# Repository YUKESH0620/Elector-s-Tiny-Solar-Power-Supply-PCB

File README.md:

# Elektor’s Solar Power Supply – Learning-Oriented Redesign

## 1. Project Overview
This project is a learning-focused redesign of **Elektor’s Tiny Solar Power Supply**. The aim is to understand the fundamentals of solar energy harvesting and low-power power supply design through hands-on schematic capture and PCB layout.

The entire circuit and PCB were redesigned from scratch using **KiCad EDA**, while referring to the original Elektor concept **strictly for educational and learning purposes**. This project emphasizes clarity, simplicity, and real-world design thinking rather than product optimization.

---

## 2. Key Learning Objectives
- Understanding **solar input conditioning** and handling variable input sources  
- Learning **power regulation basics** for low-power applications  
- Developing **component selection reasoning** based on electrical and practical constraints  
- Applying **practical PCB layout considerations** such as trace routing, grounding, and component placement  

---

## 3. Tools & Software Used
- **KiCad EDA**
  - Schematic Editor  
  - PCB Layout Editor  
  - 3D Viewer  

---

## 4. Project Files
- Schematic design files (`.kicad_sch`)  
- PCB layout files (`.kicad_pcb`)  
- 3D render images  
- Manufacturing-ready Gerber files  

---

## 5. Block-Level Working Explanation
The system starts with a **solar panel** as the primary energy source. Since solar output varies with light conditions, the input stage conditions and stabilizes this energy before it is used further.

The conditioned solar input is then passed to a **DC-DC regulation stage**, which converts the variable input voltage into a usable and stable output suitable for low-power electronic circuits. Passive components around the regulator help improve stability and efficiency.

Finally, the regulated output is made available through the output terminals, allowing it to power small loads or act as a learning reference for energy-harvesting power supplies.

This block-level flow helps beginners understand how energy moves through the system without diving into complex mathematical analysis.

---

## 6. Bill of Materials (BOM)

| S.No | Reference | Component Type        | Value / Part Number        | Footprint     | Quantity | Description |
|------|-----------|----------------------|----------------------------|---------------|----------|-------------|
| 1    | U1        | DC-DC Boost Converter| AP3015AKTR-G1               | SOT-23-5     | 1        | Step-up DC-DC converter |
| 2    | L1        | Inductor             | 10µH (LQM15AN103B0D)        | 0603         | 1        | Energy storage inductor |
| 3    | D1        | Schottky Diode       | SS14                       | SMA           | 1        | Output rectifier |
| 4    | D2        | Schottky Diode       | SS14                       | SMA           | 1        | Input protection |
| 5    | Q1        | N-Channel MOSFET     | 2N7002                     | SOT-23        | 1        | Load / power control |
| 6    | R1        | Resistor             | 1MΩ                        | 0603          | 1        | Feedback resistor |
| 7    | R2        | Resistor             | 604kΩ                      | 0603          | 1        | Feedback resistor |
| 8    | R3        | Resistor             | 100kΩ                      | 0603          | 1        | Gate pull-up |
| 9    | R4        | Resistor             | 10Ω                        | 0603          | 1        | Current limiting |
| 10   | C1        | Ceramic Capacitor    | 4.7µF, 50V, X7R            | 0805          | 1        | Input bypass capacitor |
| 11   | C2        | Ceramic Capacitor    | 22µF, 10V, X7R             | 1206          | 1        | Output bulk capacitor |
| 12   | C3        | Ceramic Capacitor    | 10µF, 50V, X7R             | 0805          | 1        | Output filtering |
| 13   | J1        | Connector            | Conn_01x02_Pin             | Through-hole  | 1        | Output connector |
| 14   | J2        | Connector            | Conn_01x02_Pin             | Through-hole  | 1        | Battery connector |
| 15   | J4        | Connector            | Conn_01x02_Pin             | Through-hole  | 1        | Solar panel input |
| 16   | SW1       | Switch               | ON/OFF (Conn_01x02_Pin)    | Through-hole  | 1        | Power enable switch |

---

## 7. Images & Renders

- **Schematic**  

- **PCB Layout**  

- **3D View**  

---

## 8. Disclaimer
This project is intended **solely for learning and educational purposes**. It is not designed or validated for commercial or critical applications.

The original concept is **inspired by Elektor**, and all redesign work presented here is independently implemented to improve understanding of solar-powered circuit design and PCB development.

---

## 9. Author
- **Name:** Yukesh S  
- **Toolchain:** KiCad EDA

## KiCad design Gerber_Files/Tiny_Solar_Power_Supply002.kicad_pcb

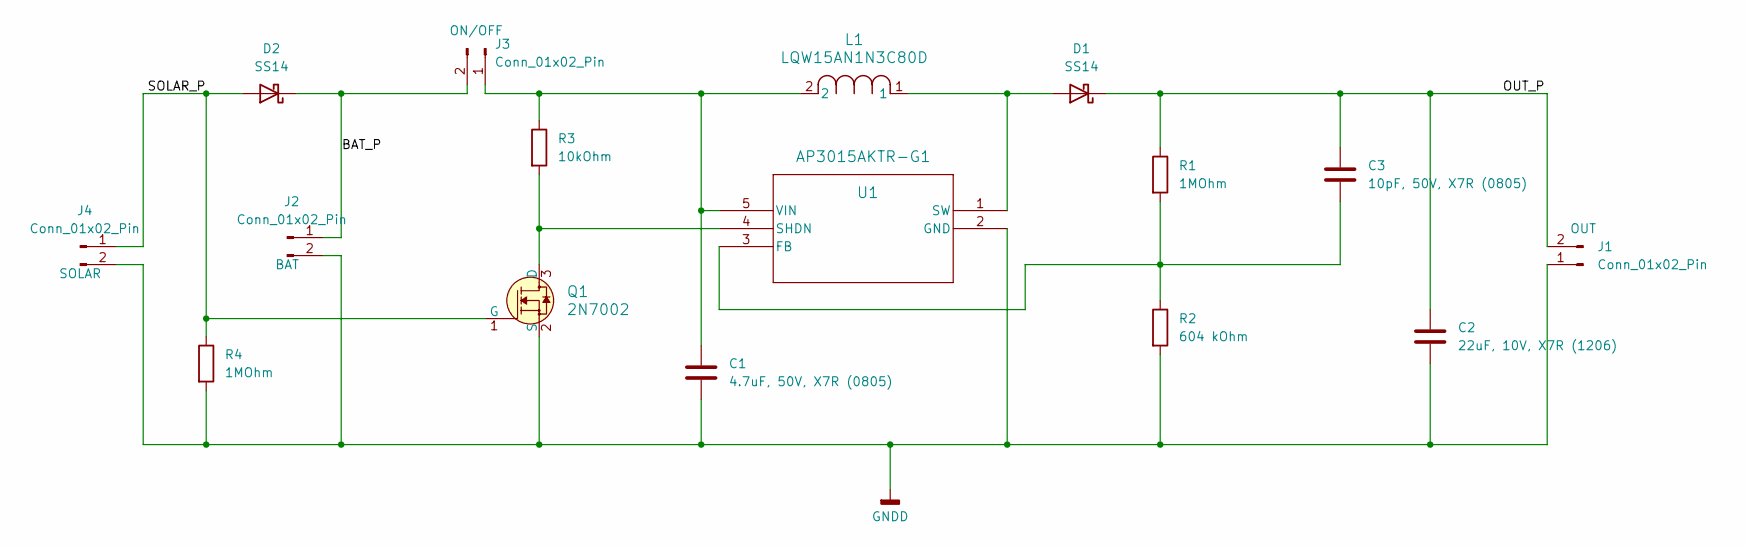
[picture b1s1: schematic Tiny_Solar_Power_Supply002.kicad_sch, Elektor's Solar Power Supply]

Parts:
C1: 4.7uF, 50V, X7R (0805); C_0805_2012Metric
C2: 22uF, 10V, X7R (1206); C_1206_3216Metric
C3: 10pF, 50V, X7R (0805); C_0805_2012Metric
D1, D2: SS14; D_SMA
J1, J2, J3: Conn_01x02_Pin; PinHeader_1x02_P2.54mm_Vertical
J4: Conn_01x02_Pin; PinHeader_1x02_P2.54mm_Horizontal
L1: LQW15AN1N3C80D; IND_LQW15_MUR
Q1: 2N7002; SOT-23-3; MPN 2N7002; Digi-Key_PN 2N7002NCT-ND
R1, R4: 1MOhm; R_0805_2012Metric
R2: 604 kOhm; R_0805_2012Metric
R3: 10kOhm; R_0805_2012Metric
U1: AP3015AKTR-G1; SOT23-5_1P55X2P9_DIO

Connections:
/BAT_P: D2.1 (K), J2.1, J3.2
/OUT_P: C2.1, C3.1, D1.1 (K), J1.2, R1.1
/SOLAR_P: D2.2 (A), J4.1, Q1.1 (G), R4.1
GNDD: C1.2, C2.2, J1.1, J2.2, J4.2, Q1.2 (S), R2.2, R4.2, U1.2 (GND)
unnamed: D1.2 (A), L1.1, U1.1 (SW)
unnamed: C1.1, J3.1, L1.2, R3.1, U1.5 (VIN)
unnamed: Q1.3 (D), R3.2, U1.4 (SHDN)
unnamed: C3.2, R1.2, R2.1, U1.3 (FB)

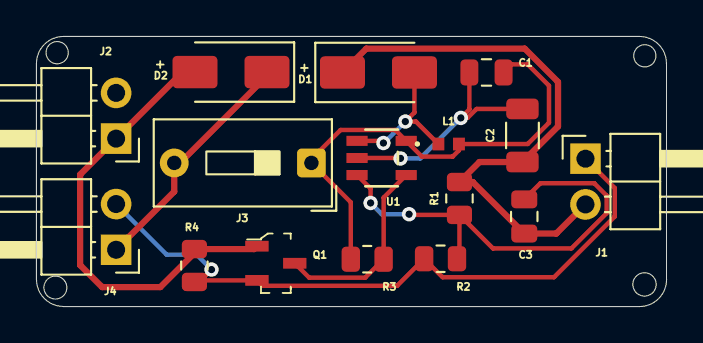
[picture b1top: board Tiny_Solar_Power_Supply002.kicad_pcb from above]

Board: 2 copper layers, 35.0 x 15.0 mm, 16 parts (0 on the bottom side), 8 nets.

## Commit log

2025-12-15 Gerber files are uploaded
2025-12-15 Kicad files are added
